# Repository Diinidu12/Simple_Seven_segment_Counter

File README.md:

# Simple_Seven_segment_Counter
This is a simple PCB designing project for follow the all the professional steps and build a quality and manufacturable PCB

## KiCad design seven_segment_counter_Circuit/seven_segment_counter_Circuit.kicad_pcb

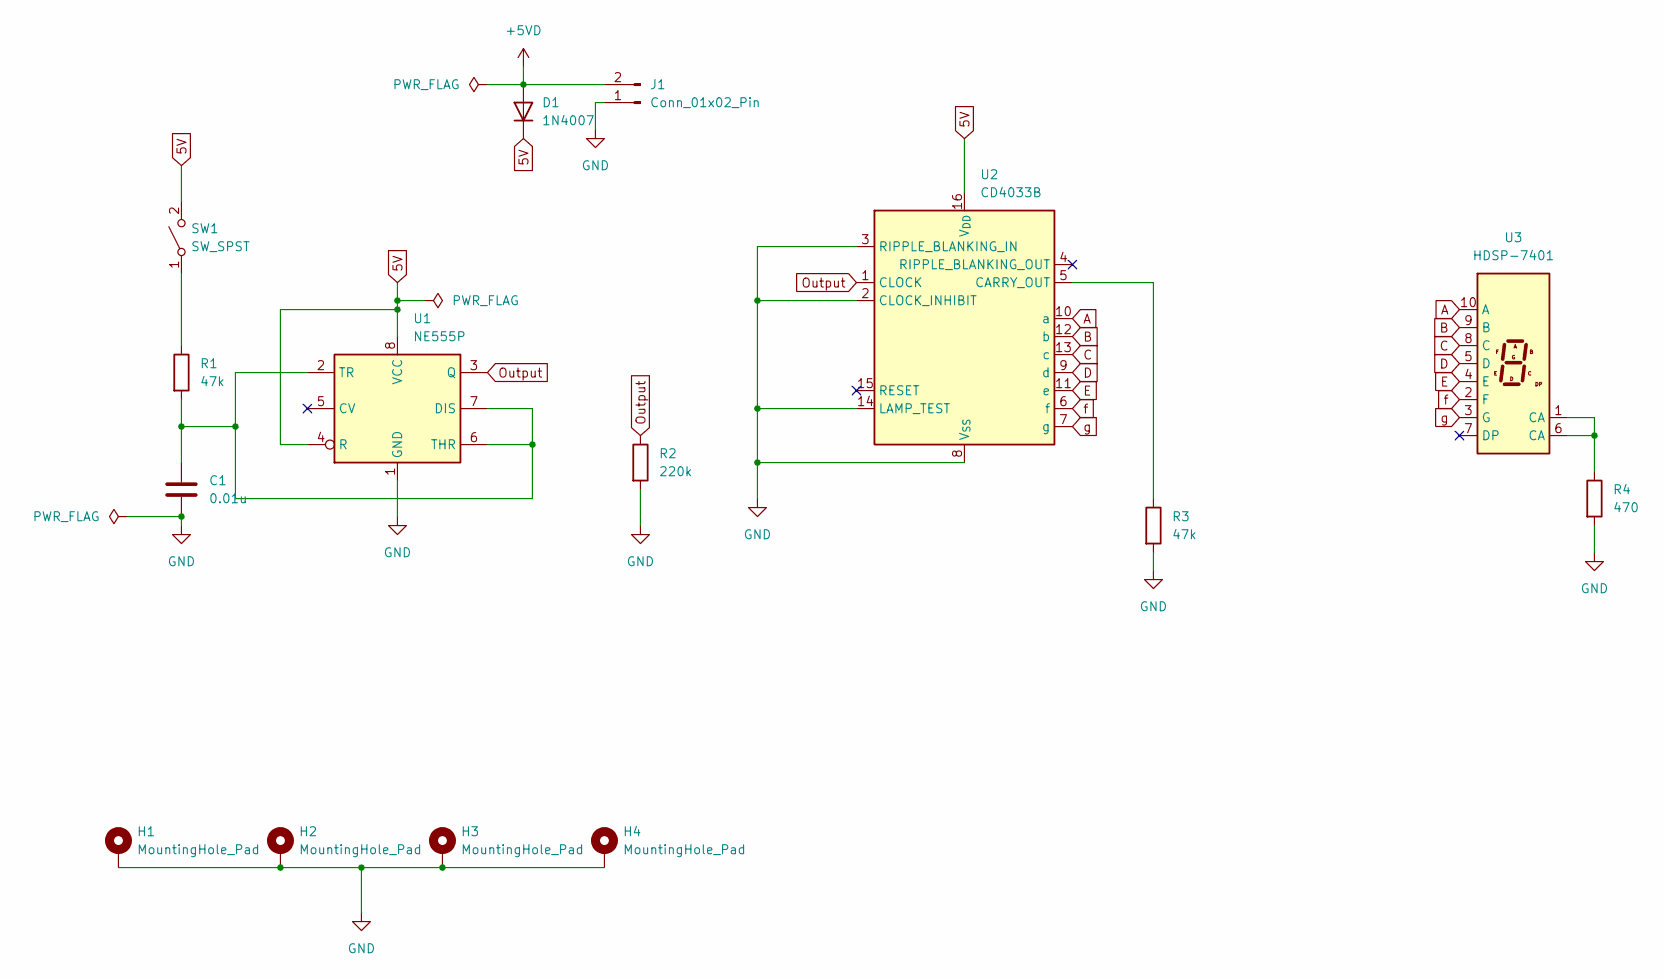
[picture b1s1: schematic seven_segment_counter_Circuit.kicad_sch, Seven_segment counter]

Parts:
C1: 0.01u; C_0805_2012Metric_Pad1.18x1.45mm_HandSolder
D1: 1N4007; D_DO-41_SOD81_P10.16mm_Horizontal
H1, H2, H3, H4: MountingHole_Pad; MountingHole_3.2mm_M3_Pad
J1: Conn_01x02_Pin; PinSocket_1x02_P2.54mm_Vertical
R1, R3: 47k; R_0805_2012Metric_Pad1.20x1.40mm_HandSolder
R2: 220k; R_0805_2012Metric_Pad1.20x1.40mm_HandSolder
R4: 470; R_0805_2012Metric_Pad1.20x1.40mm_HandSolder
SW1: SW_SPST; SW_PUSH_6mm
U1: NE555P; DIP-8_W7.62mm
U2: CD4033B; DIP-16_W7.62mm
U3: HDSP-7401

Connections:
5V: D1.1 (K), SW1.2 (B), U1.4 (R), U1.8 (VCC), U2.16 (V_{DD})
+5VD: D1.2 (A), J1.2
A: U2.10 (a), U3.10 (A)
B: U2.12 (b), U3.9 (B)
C: U2.13 (c), U3.8 (C)
D: U2.9 (d), U3.5 (D)
E: U2.11 (e), U3.4 (E)
GND: C1.2, H1.1, H2.1, H3.1, H4.1, J1.1, R2.2, R3.2, R4.2, U1.1 (GND), U2.2 (CLOCK_INHIBIT), U2.3 (RIPPLE_BLANKING_IN), U2.8 (V_{SS}), U2.14 (LAMP_TEST)
unnamed: R4.1, U3.1 (CA), U3.6 (CA)
unnamed: R1.1, SW1.1 (A)
unnamed: C1.1, R1.2, U1.2 (TR), U1.6 (THR), U1.7 (DIS)
unnamed: R3.1, U2.5 (CARRY_OUT)
Output: R2.1, U1.3 (Q), U2.1 (CLOCK)
f: U2.6 (f), U3.2 (F)
g: U2.7 (g), U3.3 (G)

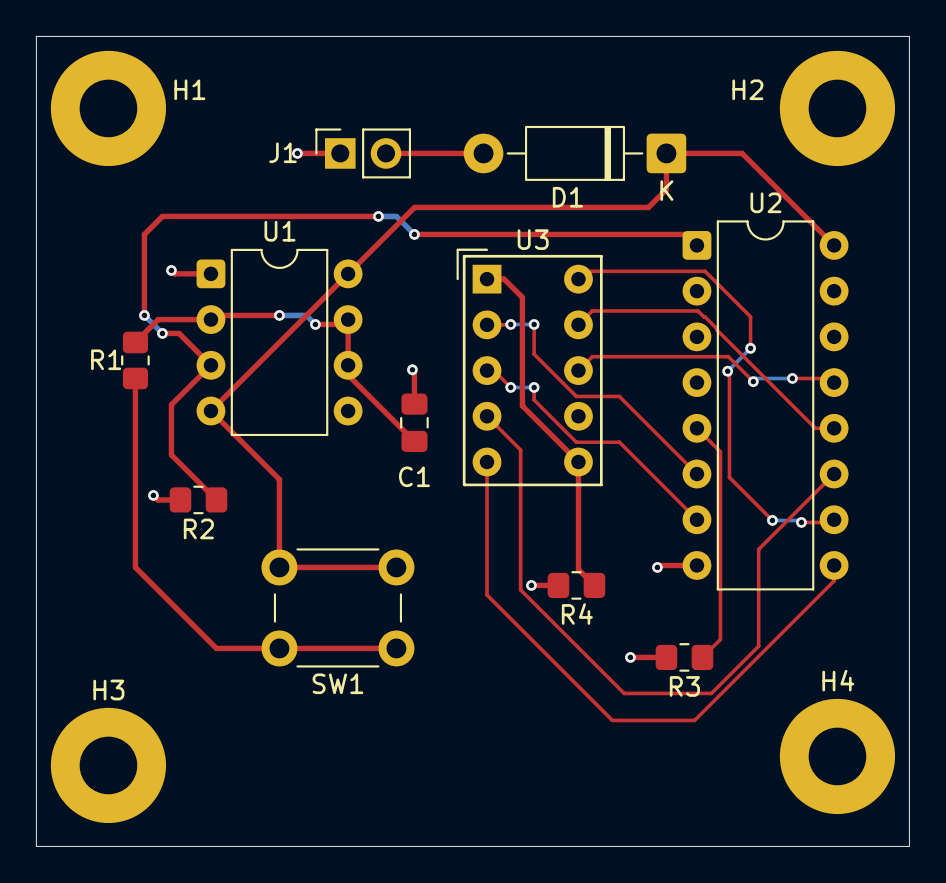
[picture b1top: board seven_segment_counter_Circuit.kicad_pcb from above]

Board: 2 copper layers, 48.5 x 45.0 mm, 15 parts (0 on the bottom side), 15 nets.
